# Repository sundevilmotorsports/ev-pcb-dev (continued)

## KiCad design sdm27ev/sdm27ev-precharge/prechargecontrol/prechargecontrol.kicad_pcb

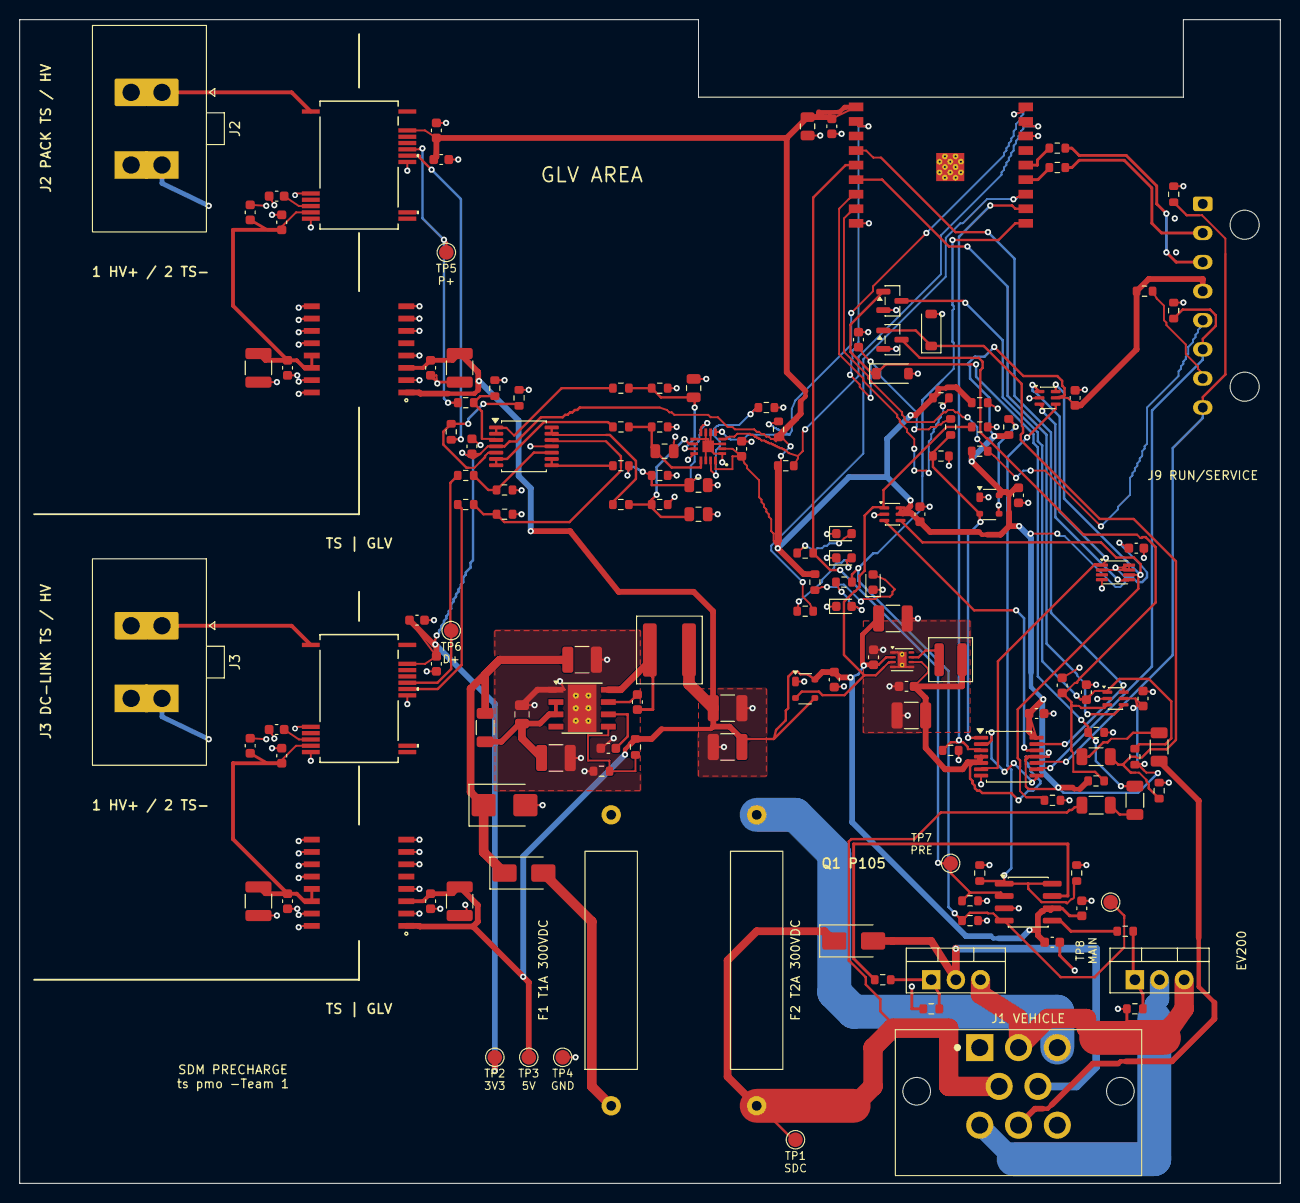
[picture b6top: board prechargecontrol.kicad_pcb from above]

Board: 4 copper layers, 130.0 x 120.0 mm, 151 parts (0 on the bottom side), 84 nets.

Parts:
C1, C5, C6: 22uF; C_1210_3225Metric
C2: 2.2uF; C_1210_3225Metric
C3, C26, C27, C28, C29, C31: 1uF; C_0603_1608Metric
C4, C9, C12, C13, C15, C17, C19, C20, C22, C30, C58, C59, C60, C61, C62: 100nF; C_0603_1608Metric
C10, C11, C14, C16: 10uF; C_1210_3225Metric
C18, C21: 100pF; C_0603_1608Metric
C32: 10u 16V; C_1210_3225Metric
C33, C35, C36, C39, C45, C55, C56, C63, C64: 100n; C_0603_1608Metric
C34: 22u 10V; C_1210_3225Metric
C37: 1u; C_0603_1608Metric
C38: 10u 10V; C_0805_2012Metric
C40, C41, C42, C43: 10uF 10V; C_0805_2012Metric
C57: 220nF; C_0805_2012Metric
D1: SS1H10-E3/61T; D_SMA
D2: SMBJ18A; D_SMB
D3: SMAJ40CA-E3/5A; D_SMA
D6: GREEN; LED_0603_1608Metric
D7: YELLOW; LED_0603_1608Metric
D8: RED; LED_0603_1608Metric
D9: GREEN / 3V3; LED_0603_1608Metric
D10, D11: 1N4148W; D_SOD-123
F1: T1A / 300VDC; Schurter_SPT_Pigtail_P30mm
F2: T2A / 300VDC; Schurter_SPT_Pigtail_P30mm
J1: 776280-1; TE_776280-1_8way
J2: PACK_VSENSE; Sabre_43160-0102_P7.49mm_Insulation
J3: DC_LINK_VSENSE; Sabre_43160-0102_P7.49mm_Insulation
J9: RUN / SERVICE; MicroFit_43650_0800_1x08_Edge
L1: 22uH; L_Coilcraft_XAL6060-XXX
L2: 2.2uH XAL4020-222MEC; L_Coilcraft_XAL4020-XXX
Q1: IRL640PBF; TO-220-3_Vertical
Q2: IRL540NPBF; TO-220-3_Vertical
Q4, Q5: BC847B; SOT-23
R1: 0R; R_1206_3216Metric
R2, R104, R108: 100k; R_0603_1608Metric
R3: 24.9k; R_0603_1608Metric
R4, R5, R18, R19, R23, R24, R25, R26, R101, R110, R111, R115: 10k; R_0603_1608Metric
R7, R8: 100; R_0603_1608Metric
R10, R11, R12, R13: 1k; R_0603_1608Metric
R14, R15, R16, R17, R100: 2.2k; R_0603_1608Metric
R21, R22: 22; R_0603_1608Metric
R27, R28, R29, R30: 2.74k 0.1%; R_0603_1608Metric
R31, R32, R33, R34: 10.0k 0.1%; R_0603_1608Metric
R35, R36, R37, R38: 20.0k 0.1%; R_0603_1608Metric
R99: 47k; R_0603_1608Metric
R102, R103, R106, R107: 10k / 0.25W; R_1206_3216Metric
R105, R109, R113, R114: 4.7k; R_0603_1608Metric
R112: 330; R_0603_1608Metric
R116, R117, R118, R119: 66.5R 0.1%; R_0603_1608Metric
TP1: SDC_COIL; TestPoint_Pad_D1.5mm
TP2, TP4: TestPoint_Pad_D1.5mm
TP3, TP5, TP6: TestPoint; TestPoint_Pad_D1.5mm
TP7: PRECHARGE_CMD; TestPoint_Pad_D1.5mm
TP8: MAIN_CMD; TestPoint_Pad_D1.5mm
U1: LMR36510ADDAR; LMR36510_DDA0008B
U2: ESP32-C3-WROOM-02-H4; ESP32_C3_WROOM_02_Edge
U3, U4: UCC12050DVER; DVE0016A
U5, U6: AMC0381D06QDFXRQ1; SSOP15_DFX_TEX
U7: TPS62162QDSGRQ1; Texas_DSG0008A_WSON-8-1EP_2x2mm_P0.5mm_EP0.9x1.6mm_ThermalV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
U8: UCC27524AQDRQ1; SOIC-8_3.9x4.9mm_P1.27mm
U9: STM811TW16F; SOT-143
U11: TLV9064QPWRQ1; TSSOP-14_4.4x5mm_P0.65mm
U19: STM811LW16F; SOT-143
U20, U24: SN74LVC1G11IDCKRQ1; SOT-363_SC-70-6
U21: SN74LVC2G14IDCKRQ1; SOT-363_SC-70-6
U22: SN74LVC1G74DCUR; VSSOP-8_2.3x2mm_P0.5mm
U23: SN74HCS11PWR; TSSOP-14_4.4x5mm_P0.65mm
U25: PAC1944; PAC1944_4MX

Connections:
+3V3: C19.1, C22.1, C27.1, C29.1, C34.1, C35.1, C36.1, C38.1, C39.1, C45.1, C56.1, C60.1, C61.1, C62.1, C63.1, C64.1, J9.4, L2.2, R13.2, R19.1, R24.1, R25.1, R26.1, R105.1, R109.1, R112.1, R113.1, R114.1, TP2.1, U2.1, U5.14, U6.14, U7.6, U9.4, U11.4, U20.5, U21.5, U22.2, U22.7, U22.8, U23.4, U23.5, U23.11, U23.14, U24.5, U24.6, U25.2, U25.16
+5V: C5.1, C6.2, C9.2, C10.2, C13.2, C14.2, C30.1, C31.1, C32.1, C33.1, C55.1, L1.1, R2.2, TP3.1, U3.1, U3.3, U4.1, U4.3, U7.2, U8.6, U19.3, U19.4
/DC_ISO_5V: C15.2, C16.2, C20.1, C28.1, U4.13, U4.14, U6.5
/DC_ISO_GND: C15.1, C16.1, C20.2, C21.2, C28.2, J3.2, U4.9, U4.10, U4.11, U4.12, U4.15, U4.16, U6.2, U6.6
/ESP32 control and service/BOOT_N: J9.5, R26.2, U2.8
/ESP32 control and service/CABLE_DM: J9.2, R21.1
/ESP32 control and service/CABLE_DP: J9.3, R22.1
/ESP32 control and service/ESP_EN: C37.1, R23.2, U2.2
/ESP32 control and service/TWAI_RX: R25.2, U2.7
/ESP32 control and service/TWAI_TX: R24.2, U2.16
/ESP32 control and service/USB_DM: R21.2, U2.13
/ESP32 control and service/USB_DP: R22.2, U2.14
/MAIN_GATE_DRIVE: R8.2, U8.5
/PACK_ISO_5V: C11.2, C12.2, C17.1, C26.1, U3.13, U3.14, U5.5
/PACK_ISO_GND: C11.1, C12.1, C17.2, C18.2, C26.2, J2.2, U3.9, U3.10, U3.11, U3.12, U3.15, U3.16, U5.2, U5.6
/PRE_GATE_DRIVE: R7.2, U8.7
/Vehicle interface and re-arm/SDC_N: C58.1, Q4.3, R105.2, U21.1
/Vehicle interface and re-arm/START_12V: J1.7, R106.1
/Vehicle interface and re-arm/START_N: C59.1, Q5.3, R109.2, U21.3
ALL_CLEAR_N: R110.1, U20.6, U22.6, U24.4
ARM_CLEAN: U20.1, U22.1, U23.6
ARM_REQUALIFIED: U20.3, U22.5
BUCK_EN: R99.1, U7.3, U19.2, U24.1
BUF_DN: R30.1, U11.13, U11.14
BUF_DP: R29.1, U11.8, U11.9
BUF_PN: R28.1, U11.6, U11.7
BUF_PP: R27.1, U11.1, U11.2
DC_OUTN: R34.1, U6.10
DC_OUTP: R33.1, TP6.1, U6.11
DIV_DN: R34.2, R38.1, U11.12
DIV_DP: R33.2, R37.1, U11.10
DIV_PN: R32.2, R36.1, U11.5
DIV_PP: R31.2, R35.1, U11.3
DRIVER_ENABLE: R16.1, R17.1, U8.1, U8.8, U20.4
GLV_12V_IN: F1.2, J1.1
GND: C1.2, C2.2, C3.2, C5.2, C6.1, C9.1, C10.1, C13.1, C14.1, C19.2, C22.2, C27.2, C29.2, C30.2, C31.2, C32.2, C33.2, C34.2, C35.2, C36.2, C37.2, C38.2, C39.2, C40.2, C41.2, C42.2, C43.2, C45.2, C55.2, C56.2, C57.2, C58.2, C59.2, C60.2, C61.2, C62.2, C63.2, C64.2, D2.2, D6.1, D7.1, D8.1, D9.1, D10.2, D11.2, J1.2, J9.1, Q1.3, Q2.3, Q4.2, Q5.2, R3.1, R4.1, R5.1, R14.2, R15.2, R16.2, R17.2, R18.2, R35.2, R36.2, R37.2, R38.2, R99.2, R100.2, R101.2, R104.2, R108.2, R110.2, R111.2, R115.2, R116.2, R117.2, R118.2, R119.2, TP4.1, U1.1, U1.9, U2.9, U2.19, U3.2, U3.4, U3.6, U3.7, U3.8, U4.2, U4.4, U4.6, U4.7, U4.8, U5.9, U6.9, U7.1, U7.4, U7.5, U7.9, U8.3, U9.1, U11.11, U19.1, U20.2, U21.2, U22.4, U23.7, U24.2, U25.1, U25.3, U25.6, U25.7, U25.9, U25.12, U25.14, U25.17
KEY_FEED: J9.7, R112.2
LED_RED_CMD: R12.2, U2.12
MAIN_CMD: R11.2, R15.1, TP8.1, U2.10, U8.4
MAIN_SW: J1.6, Q2.2
MEAS_DN: C43.1, R30.2, R119.1, U25.10
MEAS_DP: C42.1, R29.2, R118.1, U25.8
MEAS_PN: C41.1, R28.2, R117.1, U25.13
MEAS_PP: C40.1, R27.2, R116.1, U25.11
MEAS_SCL: R114.2, U2.17, U25.4
MEAS_SDA: R113.2, U2.18, U25.5
unnamed: D1.2, F1.1
unnamed: C1.1, D1.1, D2.1, R1.2
unnamed: D6.2, R10.1
unnamed: D7.2, R11.1
unnamed: D8.2, R12.1
unnamed: D9.2, R13.1
unnamed: D10.1, Q4.1, R103.2, R104.1
unnamed: D11.1, Q5.1, R107.2, R108.1
unnamed: J2.1, U5.1
unnamed: J3.1, U6.1
unnamed: Q1.1, R4.2, R7.1
unnamed: Q2.1, R5.2, R8.1
unnamed: R102.2, R103.1
unnamed: R106.2, R107.1
unnamed: C4.1, U1.7
unnamed: C2.1, C57.1, R1.1, U1.2, U1.3
unnamed: R2.1, R3.2, U1.5
unnamed: C4.2, L1.2, U1.8
unnamed: C3.1, U1.6
unnamed: C18.1, U5.4
unnamed: C21.1, U6.4
unnamed: L2.1, U7.7
OUTPUT_ARM: R100.1, U2.11, U23.3
PACK_OUTN: R32.1, U5.10
PACK_OUTP: R31.1, TP5.1, U5.11
PAC_GPIO_IDLE: R115.1, U25.15
PRECHARGE_CMD: R10.2, R14.1, TP7.1, U2.5, U8.2
PRECHARGE_SW: D3.2, J1.5, Q1.2
RAIL_OK: R18.1, R23.1, U9.2, U23.1
RESET_REQ: R19.2, U9.3
RUN_A: J9.6, R101.1, U23.9
RUN_B: J9.8, R111.1, U23.10
RUN_PERMISSION: U23.2, U23.8
SDC_12V_COIL: D3.1, F2.1, J1.4, R102.1, TP1.1
SDC_12V_IN: F2.2, J1.3
SDC_PRESENT: U2.4, U21.6, U23.13
SERVICE_CLEAR_N: U23.12, U24.3
START_REQUEST: U2.6, U21.4

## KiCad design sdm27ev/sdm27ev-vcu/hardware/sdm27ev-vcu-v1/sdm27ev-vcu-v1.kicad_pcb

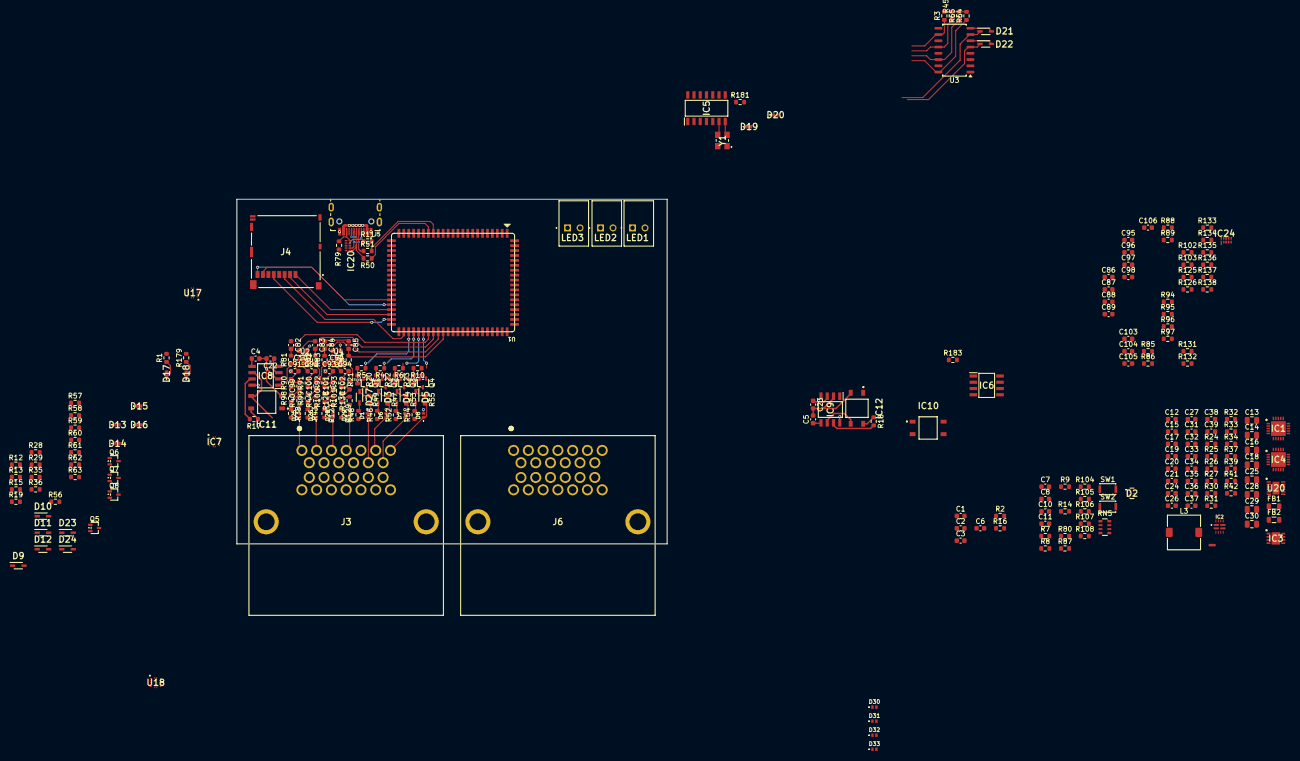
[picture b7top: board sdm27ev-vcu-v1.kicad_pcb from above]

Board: 2 copper layers, 87.4 x 70.0 mm, 253 parts (0 on the bottom side), 181 nets.

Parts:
C1, C2, C3, C4, C5, C6, C7, C11, C15, C17, C22, C23, C24, C26, C32, C34, C82, C83, C84, C85, C86, C87, C88, C89, C90, C107: 100nF; C_0603_1608Metric
C8, C19, C20, C21, C31, C33, C35, C36, C37, C38, C39: 1uF; C_0603_1608Metric
C10: 10uF; C_0603_1608Metric
C12: 10nF; C_0603_1608Metric
C13, C14, C16, C18: 10uF; C_0805_2012Metric
C25, C28: 4.7uF; C_0805_2012Metric
C27: 33pF; C_0603_1608Metric
C29, C30: 33uF; C_0805_2012Metric
C91, C92, C93, C94, C95, C96, C97, C98: 10n; C_0603_1608Metric
C99, C100, C101, C102, C103, C104, C105, C106: 20.5nF; C_0603_1608Metric
D1, D6, D7, D8, D25, D26, D28, D29, D30, D31, D32, D33: PESD24VL1BLS-QYL; PESD24VL1BLSQYL-Compact
D2: PUSB3FR6Z
D3, D4, D5, D9, D10, D11, D12, D21, D22, D23, D24, D27: BAT54WS-7-F; SOD2513X120N
D13, D14, D15, D16, D17, D18, D19, D20: PESD24VL1BLS-QYL; PESD24VL1BLSQYL
FB1, FB2: 600Ohm@100MHz ~1.4A; L_0805_2012Metric
IC1, IC4: MAX20087ATPB_VY+T; QFN50P400X400X80-21N-D
IC2: TPS2121RUXR
IC3: TLV76733QWDRBRQ1; SON65P300X300X100-9N-D
IC5: MCP2518FDT-E_SL; SOIC127P600X175-14N
IC6, IC8, IC9: TCAN3413DR; SOIC127P600X175-8N
IC7: TLV9064IRUCR; QFN40P200X200X40-14N
IC10, IC11, IC12: TLP175A_TPL,E; TLP266J
IC20, IC24: TPD4E05U06QDQARQ1; DQA_R-PUSON-N10_
J3, J6: 6437288-4; 64372884
J4: 2201778-1; 22017781
J5: USB4725-03-C-KIT; GCT_USB4730-GF-A_REVA
L3: 4.7uH; L_SXN_SMDRI62
LED1: RED; SSFLXH100LID01
LED2, LED3: GREEN; SSFLXH100LID01
NT1: NetTieGND; NetTie-2_SMD_Pad0.5mm
Q1, Q2, Q3, Q4, Q5, Q6, Q7, Q8: DMN62D2UWQ; SOT-323_SC-70
R1, R42, R46, R47, R48, R49, R52, R53, R54, R55, R56, R57, R58, R59, R60, R61, R62, R63, R179, R181, R183: 1k; R_0603_1608Metric
R2: 0; R_0603_1608Metric
R3, R45, R64, R65: 10K; R_0603_1608Metric
R4, R5, R6, R10, R12, R13, R15, R16, R17, R18, R19, R81, R82, R83, R84, R85, R86, R88, R89, R106, R107, R108: 100; R_0603_1608Metric
R7, R8, R9, R14, R38, R43, R80, R87, R104, R105, R127, R129, R131, R133, R135, R137: 10k; R_0603_1608Metric
R11, R79: 5.1k; R_0603_1608Metric
R20, R21, R22, R23, R28, R29, R35, R36, R41: 100k; R_0603_1608Metric
R24: 16.2; R_0603_1608Metric
R25, R27, R31: 5k; R_0603_1608Metric
R26, R30: 21k; R_0603_1608Metric
R32: 24.2k; R_0603_1608Metric
R33, R34: 25k; R_0603_1608Metric
R37: 34.8k; R_0603_1608Metric
R39: 19.1k; R_0603_1608Metric
R40, R44, R128, R130, R132, R134, R136, R138: 17.8K; R_0603_1608Metric
R50, R51: 27; R_0603_1608Metric
R90, R91, R92, R93, R94, R95, R96, R97: 6.49k; R_0603_1608Metric
R98, R99, R100, R101, R102, R103, R125, R126: 4.75k; R_0603_1608Metric
RN5: 10k; R_Array_Convex_4x0603
SW1, SW2: SW_Push; SW_SPST_CK_KXT3
U1: WT0132P4-A1
U2, U4: TLV9062xDSG; WSON-8-1EP_2x2mm_P0.5mm_EP0.9x1.6mm_ThermalVias
U3: TLP293-4; SOIC-16_4.55x10.3mm_P1.27mm
U17, U18: TLV9064IRUCR; QFN40P200X200X40-14N
U20: LMR51450FSQDRRRQ1; SON50P300X300X80-13N-D
Y1: ECS-3225MVQ-400-BS-TR; ECS3225MVQ400BSTR

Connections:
3.3V: C1.1, C2.1, C6.1, C7.1, C8.1, C13.1, C22.1, C23.1, C32.1, C34.1, FB1.1, IC1.11 (VDD), IC1.15 (EN), IC3.1 (OUT), IC3.3 (SNS), IC4.11 (VDD), IC4.15 (EN), IC4.16 (ADDR), IC5.14 (VDD), IC6.3 (VCC), IC8.3 (VCC), IC9.3 (VCC), J4.4 (VDD), R3.2, R7.2, R8.2, R9.2, R14.1, R45.2, R64.2, R65.2, R87.2, R104.2, R105.1, R106.1, R107.2, R108.2, Y1.1 (TRI-STATE), Y1.4 (VDD)
5V: C29.1, C30.1, FB2.1, IC2.7 (IN1), L3.2, R24.2, R26.2, R41.2, R42.2
12V: C25.1, C26.1, C28.1, R46.1, R48.1, R52.1, R54.1, R56.1, R57.1, R58.1, R59.1, U20.9 (EN), U20.10 (VIN), U20.11 (VIN_2), U20.12 (VIN_3)
/A1: C86.2, R85.2, U1.74 (GPIO16)
/A1IN: D25.1, J3.1, R38.2
/A2: C87.2, R86.2, U1.75 (GPIO17)
/A2IN: D26.1, J3.2, R43.2
/A3: C88.2, R88.2, U1.76 (GPIO18)
/A3IN: D28.1, J3.3, R127.2
/A4: C89.2, R89.2, U1.77 (GPIO19)
/A4IN: D29.1, J3.4, R129.2
/A5: C82.2, R81.2, U1.48 (GPIO49)
/A5IN: D30.1, IC24.1 (A5), R131.2
/A6: C83.2, R82.2, U1.49 (GPIO50)
/A6IN: D31.1, IC24.2 (A6), R133.2
/A7: C84.2, R83.2, U1.50 (GPIO51)
/A7IN: D32.1, IC24.4 (A7), R135.2
/A8: C85.2, R84.2, U1.51 (GPIO52)
/A8IN: D33.1, IC24.5 (A8), R137.2
/CAN1+: IC6.7 (CANH), R16.2
/CAN1-: IC6.6 (CANL), IC10.4
/CAN1_TERM: IC10.1, U1.72 (GPIO1)
/CAN2+: IC8.7 (CANH), R17.2
/CAN2-: IC8.6 (CANL), IC11.4
/CAN2_RX: IC8.4 (RXD), U1.52 (GPIO53)
/CAN2_TERM: IC11.1, U1.55 (GPIO2)
/CAN2_TX: IC8.1 (TXD), U1.54 (GPIO54)
/CAN3+: IC9.7 (CANH), R18.2
/CAN3-: IC9.6 (CANL), IC12.4
/CAN3_RX: IC9.4 (RXD), U1.65 (GPIO11)
/CAN3_TERM: IC12.1, U1.56 (GPIO3)
/CAN3_TX: IC9.1 (TXD), U1.63 (GPIO10)
/CAN/CAN1_RX: IC5.2 (RXCAN), IC6.4 (RXD)
/CAN/CAN1_STB: IC5.9 (~INT0/GPIO0/XSTBY), IC6.8 (STB), R2.2
/CAN/CAN1_TX: IC5.1 (TXCAN), IC6.1 (TXD)
/CAN_INT_1: IC5.4 (~INT), R14.2, U1.71 (GPIO0)
/CAN_SPI2_CS1: IC5.13 (NCS), U1.57 (GPIO4)
/CAN_SPI2_SCK: IC5.10 (SCK), U1.59 (GPIO6)
/CAN_SPI2_SDI: IC5.11 (SDI), U1.60 (GPIO7)
/CAN_SPI2_SDO: IC5.12 (SDO), U1.58 (GPIO5)
/DI1: R3.1, U1.69 (GPIO15), U3.10
/DI1IN: D17.1, R1.1
/DI2: R45.1, U1.68 (GPIO14), U3.12
/DI2IN: D18.1, R179.1
/DI3: R64.1, U1.66 (GPIO12), U3.16
/DI3IN: D19.1, R181.1
/DI4: R65.1, U1.67 (GPIO13), U3.14
/DI4IN: D20.1, R183.1
/DO1: R5.1, U1.44 (GPIO45)
/DO1IN: D1.1, J3.12, R49.2
/DO2: R4.1, U1.45 (GPIO46)
/DO2IN: D6.1, J3.6, R47.2
/DO3: R6.1, U1.46 (GPIO47)
/DO3IN: D7.1, J3.13, R53.2
/DO4: R10.1, U1.47 (GPIO48)
/DO4IN: D8.1, J3.7, R55.2
/DO5: R12.1, U1.24 (GPIO28)
/DO5IN: D13.1, R60.2
/DO6: R13.1, U1.25 (GPIO29)
/DO6IN: D14.1, R61.2
/DO7: R15.1, U1.26 (GPIO30)
/DO7IN: D15.1, R62.2
/DO8: R19.1, U1.27 (GPIO31)
/DO8IN: D16.1, R63.2
/ESP_LDO: R80.2, RN5.5 (R4.2), RN5.6 (R3.2), RN5.7 (R2.2), RN5.8 (R1.2), U1.32 (ESP_LDO_VO4)
/Power/A1_5V: C31.1, IC1.6 (OUT1)
/Power/A2_5V: C21.1, IC1.20 (OUT2)
/Power/A3_5V: C20.1, IC1.7 (OUT3)
/Power/A4_5V: C19.1, IC1.19 (OUT4)
/Power/A5_5V: C39.1, IC4.6 (OUT1)
/Power/A6_5V: C38.1, IC4.20 (OUT2)
/Power/A7_5V: C37.1, IC4.7 (OUT3)
/Power/A8_5V: C36.1, IC4.19 (OUT4)
/Power/SCL: IC1.14 (SCL), IC4.14 (SCL)
/Power/SDA: IC1.13 (SDA), IC4.13 (SDA)
/SD1-CLK: D2.4 (CLK), J4.5 (CLK), U1.40 (GPIO43)
/SD1-CMD: D2.5 (CMD), J4.3 (CMD), R80.1, U1.43 (GPIO44)
/SD1-DAT0: D2.1 (DAT0), J4.7 (DAT0), RN5.4 (R4.1), U1.36 (GPIO39)
/SD1-DAT1: D2.7 (DAT1), J4.8 (DAT1), RN5.3 (R3.1), U1.37 (GPIO40)
/SD1-DAT2: D2.6 (DAT2), J4.1 (DAT2), RN5.2 (R2.1), U1.38 (GPIO41)
/SD1-DAT3: D2.3 (DAT3), J4.2 (CD/DAT3), RN5.1 (R1.1), U1.39 (GPIO42)
/StatLED1: LED3.1 (K), U1.28 (GPIO32)
/StatLED2: LED2.1 (K), U1.29 (GPIO33)
/USB_D+: IC20.1 (A1), J5.A6 (D+), J5.B6 (D+), R50.2
/USB_D-: IC20.2 (A2), J5.A7 (D-), J5.B7 (D-), R51.1
A3.3V: C15.1, C16.1, C90.1, C107.1, FB1.2, U2.8 (V+), U4.8 (V+), U17.3 (V+), U18.3 (V+)
A5V: C17.1, C18.1, C33.1, C35.1, FB2.2, IC1.2 (IN), IC1.3 (IN_2), IC1.4 (IN_3), IC4.2 (IN), IC4.3 (IN_2), IC4.4 (IN_3)
GND: C1.2, C2.2, C3.2, C4.2, C5.2, C6.2, C7.2, C8.2, C10.2, C11.2, C12.2, C13.2, C14.2, C15.2, C16.2, C17.2, C18.2, C19.2, C20.2, C21.2, C22.2, C23.2, C25.2, C26.2, C28.2, C29.2, C30.2, C31.2, C32.2, C33.2, C34.2, C35.2, C36.2, C37.2, C38.2, C39.2, C82.1, C83.1, C84.1, C85.1, C86.1, C87.1, C88.1, C89.1, C90.2, C91.1, C92.1, C93.1, C94.1, C95.1, C96.1, C97.1, C98.1, C107.2, D1.2, D2.2 (GND), D6.2, D7.2, D8.2, D13.2, D14.2, D15.2, D16.2, D17.2, D18.2, D19.2, D20.2, D21.2 (A), D22.2 (A), D23.2 (A), D24.2 (A), D25.2, D26.2, D28.2, D29.2, D30.2, D31.2, D32.2, D33.2, IC1.1 (PGND_1), IC1.5 (PGND_2), IC1.9 (GND), IC1.12 (GND_2), IC1.16 (ADDR), IC1.21 (EP), IC2.3 (CP2), IC2.9 (ST), IC2.12 (GND), IC3.4 (GND), IC3.6 (GND_2), IC3.9 (EP), IC4.1 (PGND_1), IC4.5 (PGND_2), IC4.9 (GND), IC4.12 (GND_2), IC4.21 (EP), IC5.7 (VSS), IC6.2 (GND), IC8.2 (GND), IC8.8 (STB), IC9.2 (GND), IC9.8 (STB), IC10.3, IC11.3, IC12.3, IC20.3 (GND), IC20.8 (GND_2), IC24.3 (GND), IC24.8 (GND_2), J3.5, J3.9, J3.11, J4.6 (VSS), J4.11 (GND_1), J4.12 (GND_2), J4.13 (GND_3), J4.14 (GND_4), J4.15 (GND_5), J4.16 (GND_6), J5.A1 (GND), LED1.1 (K), NT1.1, Q1.2 (S), Q2.2 (S), Q3.2 (S), Q4.2 (S), Q5.2 (S), Q6.2 (S), Q7.2 (S), Q8.2 (S), R2.1, R11.2, R20.1, R21.1, R22.1, R23.1, R25.1, R27.1, R28.1, R29.1, R31.1, R32.1, R33.1, R34.1, R35.1, R36.1, R37.1, R40.1, R44.1, R79.2, R128.1, R130.1, R132.1, R134.1, R136.1, R138.1, SW1.1, SW2.2, U1.1 (GND), U1.8 (GND), U1.15 (GND), U1.18 (GND), U1.21 (GND), U1.42 (GND), U1.53 (GND), U1.64 (GND), U1.73 (GND), U1.82 (GND), U2.4 (V-), U2.9 (PAD), U3.2, U3.4, U3.6, U3.8, U3.9, U3.11, U3.13, U3.15, U4.4 (V-), U4.9 (PAD), U17.10 (V-), U18.10 (V-), U20.13 (PGND), Y1.2 (GND)
unnamed: C27.2, R42.1
unnamed: C99.1, R90.1, R98.2
unnamed: C100.1, R91.1, R99.2
unnamed: C101.1, R92.1, R100.2
unnamed: C102.1, R93.1, R101.2
unnamed: C103.1, R94.1, R102.2
unnamed: C104.1, R95.1, R103.2
unnamed: C105.1, R96.1, R125.2
unnamed: C106.1, R97.1, R126.2
unnamed: D3.2 (A), R46.2
unnamed: D3.1 (K), Q2.3 (D), R47.1
unnamed: D4.2 (A), R52.2
unnamed: D4.1 (K), Q3.3 (D), R53.1
unnamed: D5.2 (A), R54.2
unnamed: D5.1 (K), Q4.3 (D), R55.1
unnamed: D9.2 (A), R56.2
unnamed: D9.1 (K), Q5.3 (D), R60.1
unnamed: D10.2 (A), R57.2
unnamed: D10.1 (K), Q6.3 (D), R61.1
unnamed: D11.2 (A), R58.2
unnamed: D11.1 (K), Q7.3 (D), R62.1
unnamed: D12.2 (A), R59.2
unnamed: D12.1 (K), Q8.3 (D), R63.1
unnamed: D21.1 (K), R1.2, U3.7
unnamed: D22.1 (K), R179.2, U3.5
unnamed: D23.1 (K), R181.2, U3.1
unnamed: D24.1 (K), R183.2, U3.3
unnamed: D27.2 (A), R48.2
unnamed: D27.1 (K), Q1.3 (D), R49.1
unnamed: IC1.10 (ISET), R33.2
unnamed: IC2.10 (ILIM), R32.2
unnamed: IC2.5 (OV1), R26.1, R27.2
unnamed: IC2.4 (OV2), R30.1, R31.2
unnamed: IC2.6 (PR1), R24.1, R25.2
unnamed: C12.1, IC2.11 (SS)
unnamed: IC4.10 (ISET), R34.2
unnamed: IC5.6 (OSC1), Y1.3 (OUTPUT)
unnamed: C3.1, IC6.5 (V_IO)
unnamed: C4.1, IC8.5 (V_IO)
unnamed: C5.1, IC9.5 (V_IO)
unnamed: IC10.6, R16.1
unnamed: IC11.6, R17.1
unnamed: IC12.6, R18.1
unnamed: IC20.4 (A3), J5.A5 (CC1), R11.1
unnamed: IC20.5 (A4), J5.B5 (CC2), R79.1
unnamed: IC20.6 (NC_4), IC20.7 (NC_1), IC20.9 (NC_2), IC20.10 (NC_3)
unnamed: IC24.6 (NC_4), IC24.7 (NC_1), IC24.9 (NC_2), IC24.10 (NC_3)
unnamed: LED1.2 (A), R106.2
unnamed: LED2.2 (A), R107.1
unnamed: LED3.2 (A), R108.1
unnamed: Q1.1 (G), R5.2, R21.2
unnamed: Q2.1 (G), R4.2, R20.2
unnamed: Q3.1 (G), R6.2, R22.2
unnamed: Q4.1 (G), R10.2, R23.2
unnamed: Q5.1 (G), R12.2, R28.2
unnamed: Q6.1 (G), R13.2, R29.2
unnamed: Q7.1 (G), R15.2, R35.2
unnamed: Q8.1 (G), R19.2, R36.2
unnamed: R38.1, R40.2, R98.1
unnamed: R43.1, R44.2, R99.1
unnamed: R100.1, R127.1, R128.2
unnamed: R101.1, R129.1, R130.2
unnamed: R102.1, R131.1, R132.2
unnamed: R103.1, R133.1, R134.2
unnamed: R125.1, R135.1, R136.2
unnamed: R126.1, R137.1, R138.2
unnamed: R8.1, R9.1, SW1.2, SW2.1, U1.31 (GPIO35), U1.70 (CHIP_PU)
unnamed: R7.1, U1.33 (GPIO36)
unnamed: R51.2, U1.16 (USB_DM)
unnamed: R50.1, U1.17 (USB_DP)
unnamed: C91.2, R90.2, U2.3 (+)
unnamed: C99.2, R81.1, U2.1, U2.2 (-)
unnamed: C92.2, R91.2, U2.5 (+)
unnamed: C100.2, R82.1, U2.6 (-), U2.7
unnamed: C93.2, R92.2, U4.3 (+)
unnamed: C101.2, R83.1, U4.1, U4.2 (-)
unnamed: C94.2, R93.2, U4.5 (+)
unnamed: C102.2, R84.1, U4.6 (-), U4.7
unnamed: C95.2, R94.2, U18.1 (IN1+)
unnamed: C103.2, R85.1, U18.2 (IN1-), U18.14 (OUT1)
unnamed: C96.2, R95.2, U18.4 (IN2+)
unnamed: C104.2, R86.1, U18.5 (IN2-), U18.6 (OUT2)
unnamed: C97.2, R96.2, U18.9 (IN3+)
unnamed: C105.2, R88.1, U18.7 (OUT3), U18.8 (IN3-)
unnamed: C98.2, R97.2, U18.11 (IN4+)
unnamed: C106.2, R89.1, U18.12 (IN4-), U18.13 (OUT4)
unnamed: NT1.2, R39.1, U20.8 (AGND)
unnamed: C24.1, U20.4 (BOOT)
unnamed: C27.1, R39.2, R41.1, U20.7 (FB)
unnamed: R37.2, U20.6 (RT)
unnamed: C24.2, L3.1, U20.1 (SW), U20.2 (SW_2), U20.3 (SW_3)
VBUS: IC2.2 (IN2), J5.A4 (VBUS), R30.2
VCC: C10.1, C11.1, C14.1, IC2.1 (OUT_1), IC2.8 (OUT_2), IC3.5 (EN), IC3.8 (IN), U1.41 (VCC)

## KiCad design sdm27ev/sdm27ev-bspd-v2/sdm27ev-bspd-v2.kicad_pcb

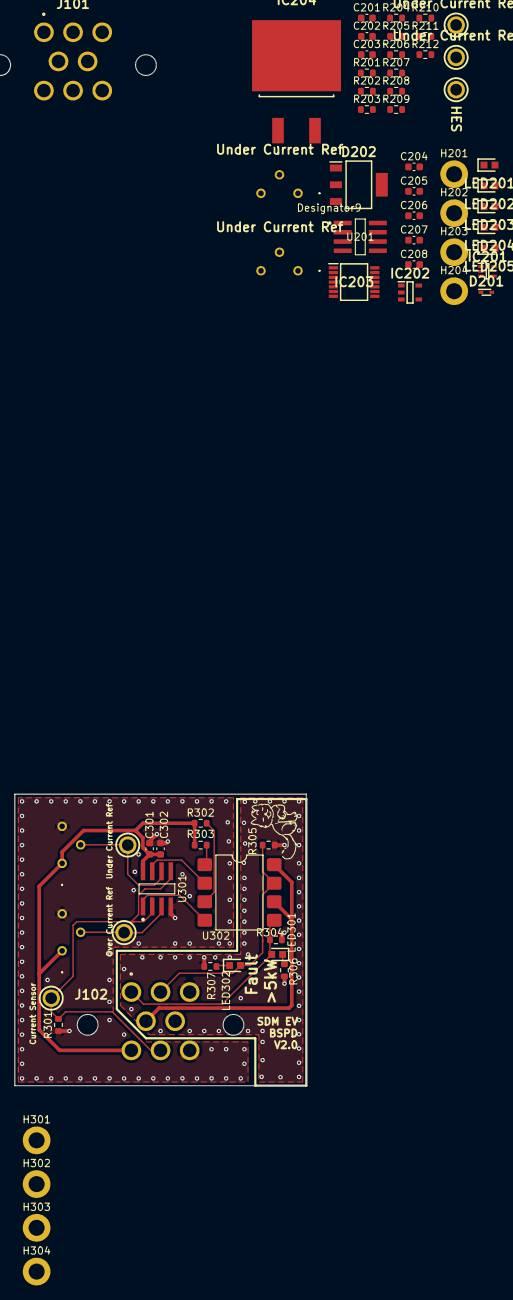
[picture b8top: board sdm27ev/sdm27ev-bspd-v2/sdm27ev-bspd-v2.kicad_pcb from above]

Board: 2 copper layers, 40.0 x 40.0 mm, 66 parts (0 on the bottom side), 33 nets.

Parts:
C201, C203, C206: 1uF; C_0603_1608Metric
C202: 10uF; C_0603_1608Metric
C204, C301: 1µF; C_0603_1608Metric
C205, C302: 100nF; C_0603_1608Metric
C207: 0.33uF; C_0603_1608Metric
C208: 0.1uF; C_0603_1608Metric
D201: BAT54XV2T1G; SODFL1608X70N
D202: X0202MN_5BA4; SOT230P700X190-4N
Dylan Shah: LOGO; Robocat 10x10mm
H201, H202, H203, H204, H301, H302, H303, H304: MountingHole; MountingHole_2.2mm_M2_DIN965_Pad
IC201: 74AHC1G08; SOT65P212X110-5L
IC202: SN74LVC1G17DBVRG4; SOT95P280X145-5L
IC203: SN74HC32PWR; SOP65P640X120-14L
IC204: L7805ACD2T-TR; L7805ACD2TTR
J101, J102: 776280-1
LED201, LED202, LED203, LED204, LED205, LED301, LED302: 150060GS75000; LEDC1608X80N
R201, R301, R304, R305: 10K; R_0603_1608Metric
R202: 39K; R_0603_1608Metric
R203: 100; R_0603_1608Metric
R204, R205: 1k; R_0603_1608Metric
R206, R207, R211, R212, R306, R307: 4.7k; R_0603_1608Metric
R208: 510; R_0603_1608Metric
R209, R210: 100k; R_0603_1608Metric
R302, R303: 680; R_0603_1608Metric
RED_TP201, RED_TP202, RED_TP301, RED_TP302: 5005
U201, U301: TLV9022QDRQ1; TLV9022QDRQ1-IPC_A
U302: LTV-827S; SMDIP-8_W9.53mm
VR201, VR202, VR301, VR302: 10k; 3386P1103TLF
WHITE_TP201, WHITE_TP301: 5007

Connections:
+5V: C201.1, C203.1, C204.1, C205.1, C206.1, C208.2, IC201.5 (VCC), IC202.5 (VCC), IC203.9 (3A), IC203.10 (3B), IC203.12 (4A), IC203.13 (4B), IC203.14 (VCC), IC204.3 (OUT), J101.5, J102.4, R204.2, R205.1, R208.1, R209.2, R210.2, U201.8 (VCC), U302.6, U302.8, VR201.1 (CCW), VR202.1 (CCW)
+5V_BMS: C301.1, C302.1, J102.6, R302.1, R303.2, U301.8 (VCC), VR301.1 (CCW), VR302.1 (CCW)
+12V: C207.2, IC204.1 (IN), J101.1
/CH1_CURRENT SENSOR: J102.7, R301.2, U301.2 (IN1-), U301.5 (IN2+), WHITE_TP301.1 (1_1)
/Current Sensor Fault: IC203.1 (1A), J101.7, J102.2, LED204.2 (A), LED302.2 (A), R210.1, R305.1, U302.7
/Current Sensor Sub-Board/Over Current Ref: RED_TP301.1 (1_1), U301.3 (IN1+), VR301.2 (Wiper)
/Current Sensor Sub-Board/Under Current Ref: RED_TP302.1 (1_1), U301.6 (IN2-), VR302.2 (Wiper)
/Current Sensor Sub-Board/~Current Sensor Fault: U301.7 (OUT2), U302.2
/Current Sensor Sub-Board/~Over Current Fault: U301.1 (OUT1), U302.4
/Main Board/Brake Connection Fault Ref: RED_TP202.1 (1_1), U201.5 (IN2+), VR202.2 (Wiper)
/Main Board/Brake Sensor: J101.4, R201.2, U201.3 (IN1+), U201.6 (IN2-), WHITE_TP201.1 (1_1)
/Main Board/Break Disconnected: IC203.2 (1B), LED201.2 (A), R204.1, U201.7 (OUT2)
/Main Board/Combined Fault Line: D202.3 (G), IC203.6 (2Y)
/Main Board/HB*5kW_FAULT: C202.1, D201.2 (A), IC202.2 (A), R202.2
/Main Board/Hard Breaking: IC201.2 (A), LED202.2 (A), R205.2, U201.1 (OUT1)
/Main Board/Over power and break for 0.25s: IC202.4 (Y), IC203.5 (2B)
/Main Board/~BSPD Fault: D202.2 (A_1), D202.4 (A_2), J101.2, LED203.1 (K)
/POWER OVER FAUT: IC201.1 (B), J101.6, J102.1, LED205.2 (A), LED301.2 (A), R209.1, R304.2, U302.5
GND: C201.2, C202.2, C203.2, C204.2, C205.2, C206.2, C207.1, C208.1, D202.1 (K), IC201.3 (GND), IC202.3 (GND), IC203.7 (GND), IC204.2 (GND), J101.3, J101.8, J102.3, R201.1, R206.2, R207.2, R211.2, R212.2, R304.1, R305.2, R306.2, R307.2, U201.4 (GND), VR201.3 (CW), VR202.3 (CW)
GND_BMS: C301.2, C302.2, J102.8, R301.1, U301.4 (GND), VR301.3 (CW), VR302.3 (CW)
unnamed: D201.1 (K), R203.2
unnamed: IC201.4 (Y), R202.1, R203.1
unnamed: IC203.3 (1Y), IC203.4 (2A)
unnamed: LED201.1 (K), R206.1
unnamed: LED202.1 (K), R207.1
unnamed: LED203.2 (A), R208.2
unnamed: LED204.1 (K), R211.1
unnamed: LED205.1 (K), R212.1
unnamed: LED301.1 (K), R306.1
unnamed: LED302.1 (K), R307.1
unnamed: R302.2, U302.3
unnamed: R303.1, U302.1
unnamed: RED_TP201.1 (1_1), U201.2 (IN1-), VR201.2 (Wiper)
